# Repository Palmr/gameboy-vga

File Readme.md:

# FPGA Game Boy Framebuffer

My attempts at hooking in to the Game Boy LCD cable to sniff frame data.

Currently only looking at the Game Boy Pocket as I have one with screen rot and would ideally like to add other output options or replace the screen with something else.

## Requirements

Currently running off an [Lattice Semi](http://www.latticesemi.com) FPGA on a [TinyFPGA BX](https://github.com/tinyfpga/TinyFPGA-BX).

After cloning this repository make sure to pull in the submodule for building/flashing the RTL

```bash
git submodule update --init
```

This should pull in my forked version of the excellent [fpga-tools](https://github.com/pwmarcz/fpga-tools/) submodule by [Paweł Marczewski](https://github.com/pwmarcz).

Required software:

- [Project IceStorm](http:///www.clifford.at/icestorm/)
- [iceBurn](https://github.com/davidcarne/iceBurn)
- GTKWave (for `make sim` target)

## RTL

Experiments documented in [see the rtl/exploration/Readme.md](./rtl/exploration/Readme.md).

Actual code is in the RTL folder currently.

## Devlog

Gameboy MGB (pocket) LCD cable pinout:

	1 - GND
	2 - Control
	3 - Data latch
	4 - Horiz Sync
	5 - Data 0
	6 - Data 1
	7 - Clock
	8 - Alt Sig
	9 - V5
	10 - V3
	11 - V2
	12 - Data latch
	13 - VSYNC
	14 - Vcc (5 volts)
	15 - Alt sign
	16 - V1
	17 - V4
	18 - V5

I connected that to the FPGA and passed the signals through to check the voltages were all okay and the FPGA was registering the signals as expected.

Trace from [frame_counter.v](rtl/exploration/frame_counter.v) showing `0x3B` transitions of the `VSYNC` signal per second, aka 59fps:

Trace from [pixels_per_frame_counter.v](rtl/exploration/pixels_per_frame_counter.v) showing `0x59FF` pixel clock transitions per `VSYNC`:

VGA core started with some timing bars to check my timings and pixel counts added up.

That worked so I moved on to a 2 bit grayscale colour system using resistor values to tweak voltage levels for VGA.

By this time my desk is a mess.

Protoboard was soldered together for a cleaner setup after breadboarding.

First attempts at capturing and displaying the framebuffer from the GameBoy LCD showed some severe timing issues.

It also showed the colour palette was inverted.

Fixing the palette was simple, but finding thr source of the HSYNC skew was tougher.

Eventually traced my HSYNC issues down to a badly terminated HSYNC connection from the LCD. Still the game looked a little slanted, especially at the lower part of the screen.

That was down to me incorrectly counting pixels and underfilling lines. With this fixed it's almost passable.

With everything working I could remove my debug information and add a 2x scaling to the display, and centre it to the screen.

:tada:

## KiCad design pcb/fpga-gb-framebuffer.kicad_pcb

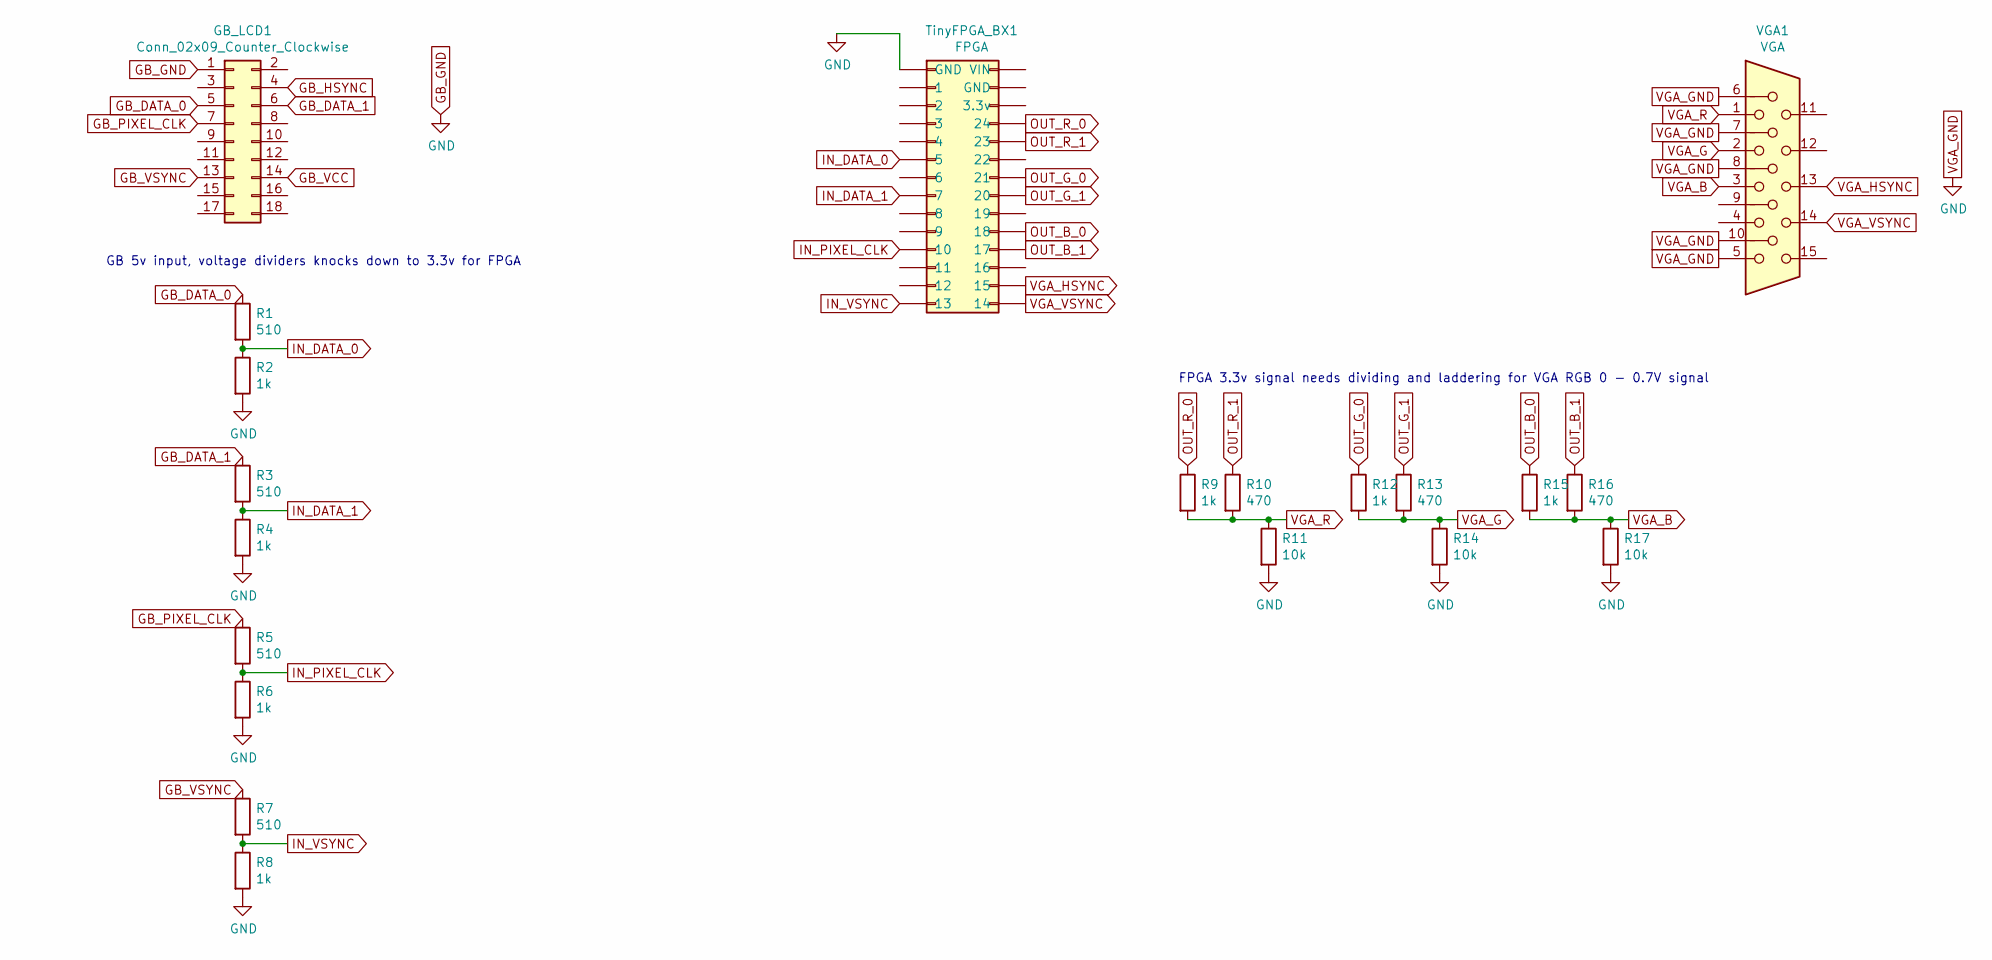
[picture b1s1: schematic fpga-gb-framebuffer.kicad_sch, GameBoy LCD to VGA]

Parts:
GB_LCD1: Conn_02x09_Counter_Clockwise; PinHeader_2x09_P2.54mm_Vertical
R1, R3, R5, R7: 510; R_Axial_DIN0204_L3.6mm_D1.6mm_P7.62mm_Horizontal
R2, R4, R6, R8, R9, R12, R15: 1k; R_Axial_DIN0204_L3.6mm_D1.6mm_P7.62mm_Horizontal
R10, R13, R16: 470; R_Axial_DIN0204_L3.6mm_D1.6mm_P7.62mm_Horizontal
R11, R14, R17: 10k; R_Axial_DIN0204_L3.6mm_D1.6mm_P7.62mm_Horizontal
TinyFPGA_BX1: FPGA; TinyFPGA_BX
VGA1: VGA; DSUB-15-HD_Female_Vertical_P2.29x1.98mm_MountingHoles

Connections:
GB_DATA_0: GB_LCD1.5, R1.1
GB_DATA_1: GB_LCD1.6, R3.1
GB_GND: GB_LCD1.1, R2.2, R4.2, R6.2, R8.2, R11.2, R14.2, R17.2, TinyFPGA_BX1.1 (GND), VGA1.5, VGA1.6, VGA1.7, VGA1.8, VGA1.10
GB_HSYNC: GB_LCD1.4
GB_PIXEL_CLK: GB_LCD1.7, R5.1
GB_VCC: GB_LCD1.14
GB_VSYNC: GB_LCD1.13, R7.1
IN_DATA_0: R1.2, R2.1, TinyFPGA_BX1.6 (5)
IN_DATA_1: R3.2, R4.1, TinyFPGA_BX1.8 (7)
IN_PIXEL_CLK: R5.2, R6.1, TinyFPGA_BX1.11 (10)
IN_VSYNC: R7.2, R8.1, TinyFPGA_BX1.14 (13)
OUT_B_0: R15.1, TinyFPGA_BX1.19 (18)
OUT_B_1: R16.1, TinyFPGA_BX1.18 (17)
OUT_G_0: R12.1, TinyFPGA_BX1.22 (21)
OUT_G_1: R13.1, TinyFPGA_BX1.21 (20)
OUT_R_0: R9.1, TinyFPGA_BX1.25 (24)
OUT_R_1: R10.1, TinyFPGA_BX1.24 (23)
VGA_B: R15.2, R16.2, R17.1, VGA1.3
VGA_G: R12.2, R13.2, R14.1, VGA1.2
VGA_HSYNC: TinyFPGA_BX1.16 (15), VGA1.13
VGA_R: R9.2, R10.2, R11.1, VGA1.1
VGA_VSYNC: TinyFPGA_BX1.15 (14), VGA1.14

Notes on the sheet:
GB 5v input, voltage dividers knocks down to 3.3v for FPGA
FPGA 3.3v signal needs dividing and laddering for VGA RGB 0 - 0.7V signal

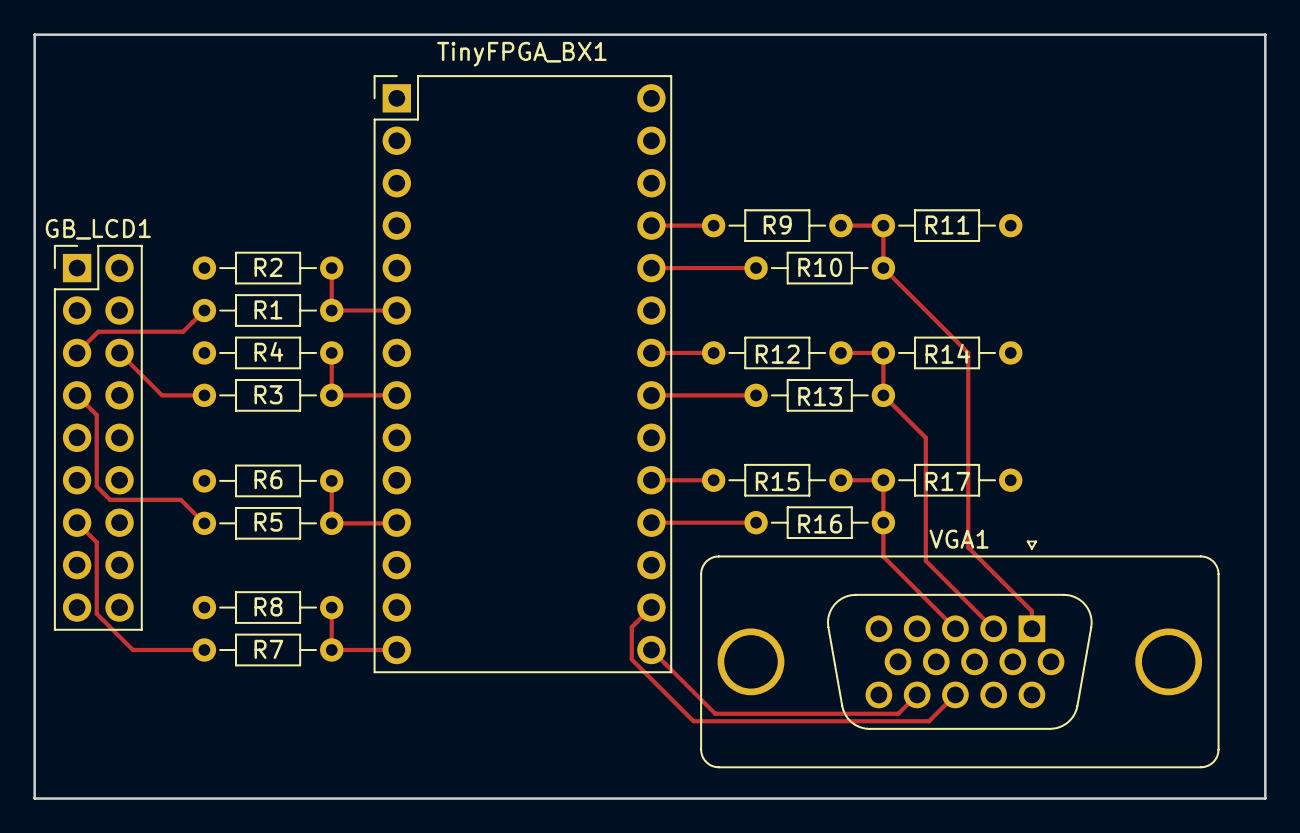
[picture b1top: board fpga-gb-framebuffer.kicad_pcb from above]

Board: 2 copper layers, 73.7 x 45.7 mm, 20 parts (0 on the bottom side), 20 nets.

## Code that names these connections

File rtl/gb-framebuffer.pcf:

## INPUTS

# FPGA clock
set_io CLK_16MHz    B2

# 2x Scaling
set_io scaling_x2   A2  # BX:1

# GB LCD Inputs
set_io GB_DAT[0]    C1  # BX:5  <- white <- MGB LCD pin 5
set_io GB_DAT[1]    D1  # BX:7  <- white <- MGB LCD pin 6
set_io GB_PX_CLK    G2  # BX:10 <- orange <- MGB LCD pin 7
set_io GB_HSYNC     J1  # BX:12 <- n/a <- MGB LCD pin 4 # Currently not connected on board
set_io GB_VSYNC     H2  # BX:13 <- yellow <- MGB LCD pin 13

## OUTPUTS

set_io vga_r[0]     A6  # RED BX:24 -> 1k/10k -> VGA:1
set_io vga_r[1]     B6  # RED BX:23 -> 470/10k -> VGA:1

set_io vga_g[0]     B7  # GREEN BX:21 -> 1k/10k -> VGA:2
set_io vga_g[1]     A8  # GREEN BX:20 -> 470/10k -> VGA:2

set_io vga_b[0]     A9  # BLUE BX:18 -> 1k/10k -> VGA:3
set_io vga_b[1]     C9  # BLUE BX:17 -> 470/10k -> VGA:3

set_io vga_hs       D9  # HSYNC BX:15 -> purple/orange -> VGA:13
set_io vga_vs       H9  # VSYNC BX:14 -> yellow -> VGA:14

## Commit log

2018-12-17 Readme update
2018-12-18 Added a pixels per frame counter
2018-12-18 Fixed missing slash from link
2018-12-30 moved to fpga-tools iCEblink40 branch
2019-01-01 updated fpga-tools
2019-01-01 VGA framebuffer test
2019-01-01 Updated fpga-tools (now using nextpnr rather than arachne)
2019-01-06 Add UART test
2019-01-06 VGA test patterns
2019-01-06 First stab, sync issues however
2019-01-13 kicad first tinyfpga board
2019-01-13 rtl tweaks
2019-01-15 formatting
2019-01-16 Update blink for TinyFPGA BX
2019-01-16 Updated PCB design
2019-01-16 Updated framecounter for TinyFPGA BX
2019-01-16 Schematic update with tinyfpga symbol and pin assignment update for VGA
2019-01-16 Fixed fab and silskcreen layouts
2019-01-16 kicad project update
2019-01-17 Updated for kicad design
2019-01-17 Doube gb res in vga out
2019-06-29 split out vga module and made a background test
2019-06-29 gitignore
2019-06-29 Revisit exploration-vga
2019-06-29 vga module on negedge so use can be done on posedge
2019-11-30 Latest bits
2020-11-22 Add VGA test with 2x scaling
2020-11-22 test code
2020-11-24 Working code (mostly)
2020-11-24 update bits
2020-11-24 Empty the empty-framebuffer
2020-11-25 naming updates
2020-11-25 Add vsync on no pixels seen for a while rather than on gb_vsync
2023-02-09 Updated readme with a devlog
2023-02-09 refresh pcb with newer kikad
2023-02-09 update fpga-tools submodule
